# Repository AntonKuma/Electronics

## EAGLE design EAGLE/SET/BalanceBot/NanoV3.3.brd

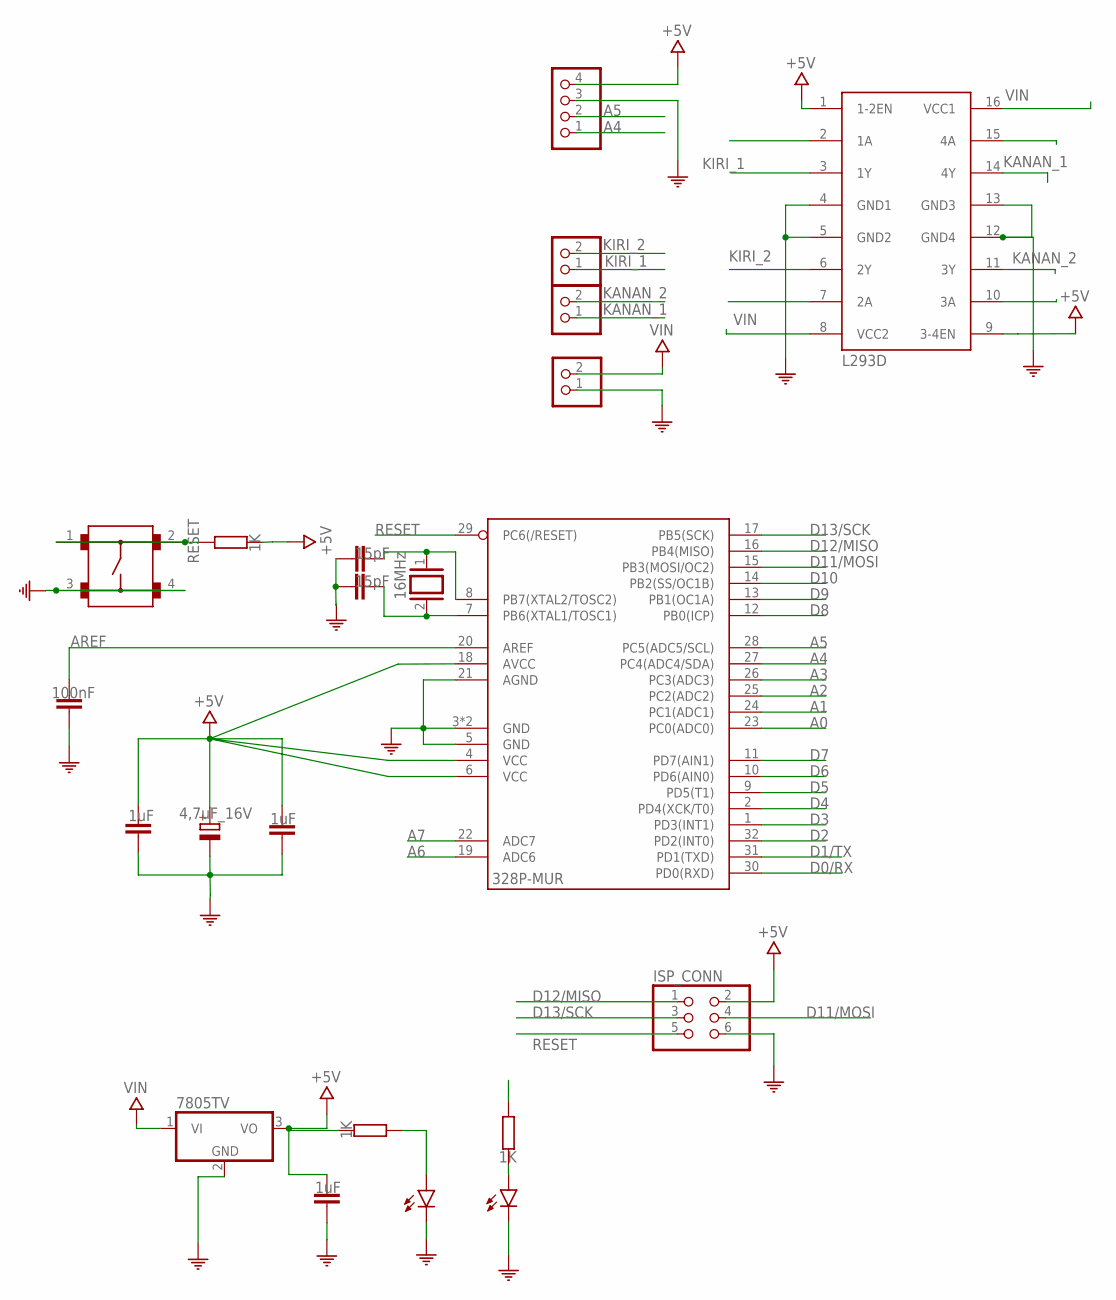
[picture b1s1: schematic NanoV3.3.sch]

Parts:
C1: 4,7uF_16V; B45181A
C2, C4: 15pF; C025-024X044
C3, C9, C10: 1uF; C025-024X044
C6: 100nF; C025-024X044
GYRO: PINHD-1X4; 1X04
IC1: L293D; DIL16
IC3: 328P-MUR; VQFN32
IC4: 7805TV; TO220V
ISP_CONN: 0114_PH254-203DF118A00V; 2X03
J3: INPUT; 1X02
J6: MOTOR; 1X02
L: DATA; LED3MM
MOTOR: MOTOR; 1X02
PWR: POWER; LED3MM
Q1: 16MHz; QS
R1, R2, R3: 1K; 0204/5
SW1: RESET; B3F-1000

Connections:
+5V: C1.+, C3.2, C9.2, C10.2, GYRO.4, IC1.1 (1-2EN), IC1.9 (3-4EN), IC3.4 (VCC), IC3.6 (VCC), IC3.18 (AVCC), IC4.3 (VO), ISP_CONN.2, R1.2, R2.2
A0: IC3.23 (PC0(ADC0))
A1: IC3.24 (PC1(ADC1))
A2: IC3.25 (PC2(ADC2))
A3: IC3.26 (PC3(ADC3))
A4: GYRO.1, IC3.27 (PC4(ADC4/SDA))
A5: GYRO.2, IC3.28 (PC5(ADC5/SCL))
A6: IC3.19 (ADC6)
A7: IC3.22 (ADC7)
AREF: C6.1, IC3.20 (AREF)
COM: C1.-, C2.1, C3.1, C4.1, C6.2, C9.1, C10.1, GYRO.3, IC1.4 (GND1), IC1.5 (GND2), IC1.12 (GND4), IC1.13 (GND3), IC3.3 (GND), IC3.5 (GND), IC3.21 (AGND), IC3.33 (GND), IC4.2 (GND), ISP_CONN.6, J3.1, L.K (C), PWR.K (C), SW1.3, SW1.4
D0/RX: IC3.30 (PD0(RXD))
D1/TX: IC3.31 (PD1(TXD))
D2: IC3.32 (PD2(INT0))
D3: IC3.1 (PD3(INT1))
D4: IC3.2 (PD4(XCK/T0))
D5: IC3.9 (PD5(T1))
D6: IC1.2 (1A), IC3.10 (PD6(AIN0))
D7: IC3.11 (PD7(AIN1))
D8: IC3.12 (PB0(ICP))
D9: IC1.7 (2A), IC3.13 (PB1(OC1A))
D10: IC1.10 (3A), IC3.14 (PB2(SS/OC1B))
D11/MOSI: IC1.15 (4A), IC3.15 (PB3(MOSI/OC2)), ISP_CONN.4
D12/MISO: IC3.16 (PB4(MISO)), ISP_CONN.1
D13/SCK: IC3.17 (PB5(SCK)), ISP_CONN.3, R3.1
KANAN_1: IC1.14 (4Y), J6.1
KANAN_2: IC1.11 (3Y), J6.2
KIRI_1: IC1.3 (1Y), MOTOR.1
KIRI_2: IC1.6 (2Y), MOTOR.2
unnamed: C4.2, IC3.7 (PB6(XTAL1/TOSC1)), Q1.2
unnamed: C2.2, IC3.8 (PB7(XTAL2/TOSC2)), Q1.1
unnamed: PWR.A, R2.1
unnamed: L.A, R3.2
RESET: IC3.29 (PC6(/RESET)), ISP_CONN.5, R1.1, SW1.1, SW1.2
VIN: IC1.8 (VCC2), IC1.16 (VCC1), IC4.1 (VI), J3.2

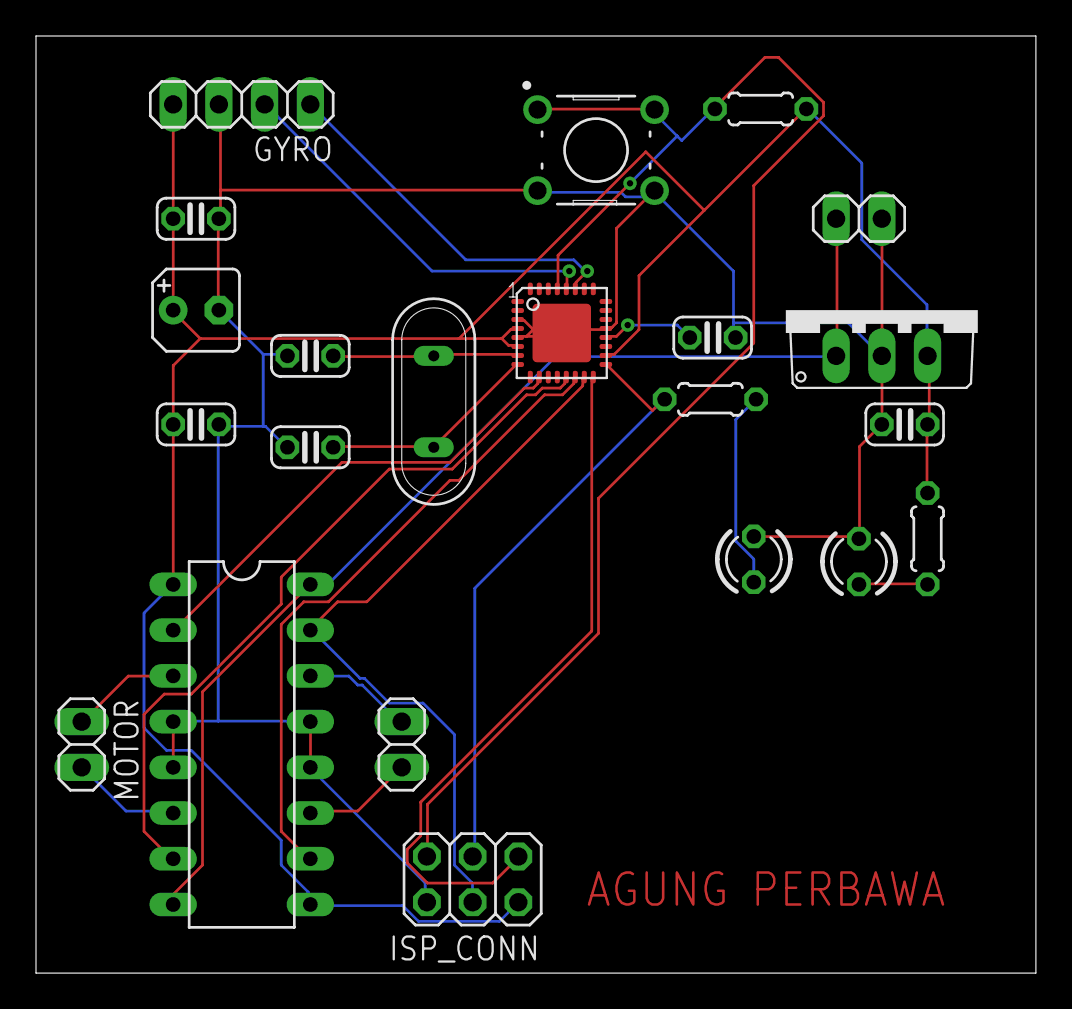
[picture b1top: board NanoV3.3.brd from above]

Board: 2 copper layers, 55.5 x 52.1 mm, 22 parts (0 on the bottom side), 21 nets.

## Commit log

2021-08-05 05.Aug.2021 | 12.00

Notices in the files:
parts and their libraries:
Arduino-ucs: Copyright (c) 2016-2017 Arduino LLC.  All right reserved.
